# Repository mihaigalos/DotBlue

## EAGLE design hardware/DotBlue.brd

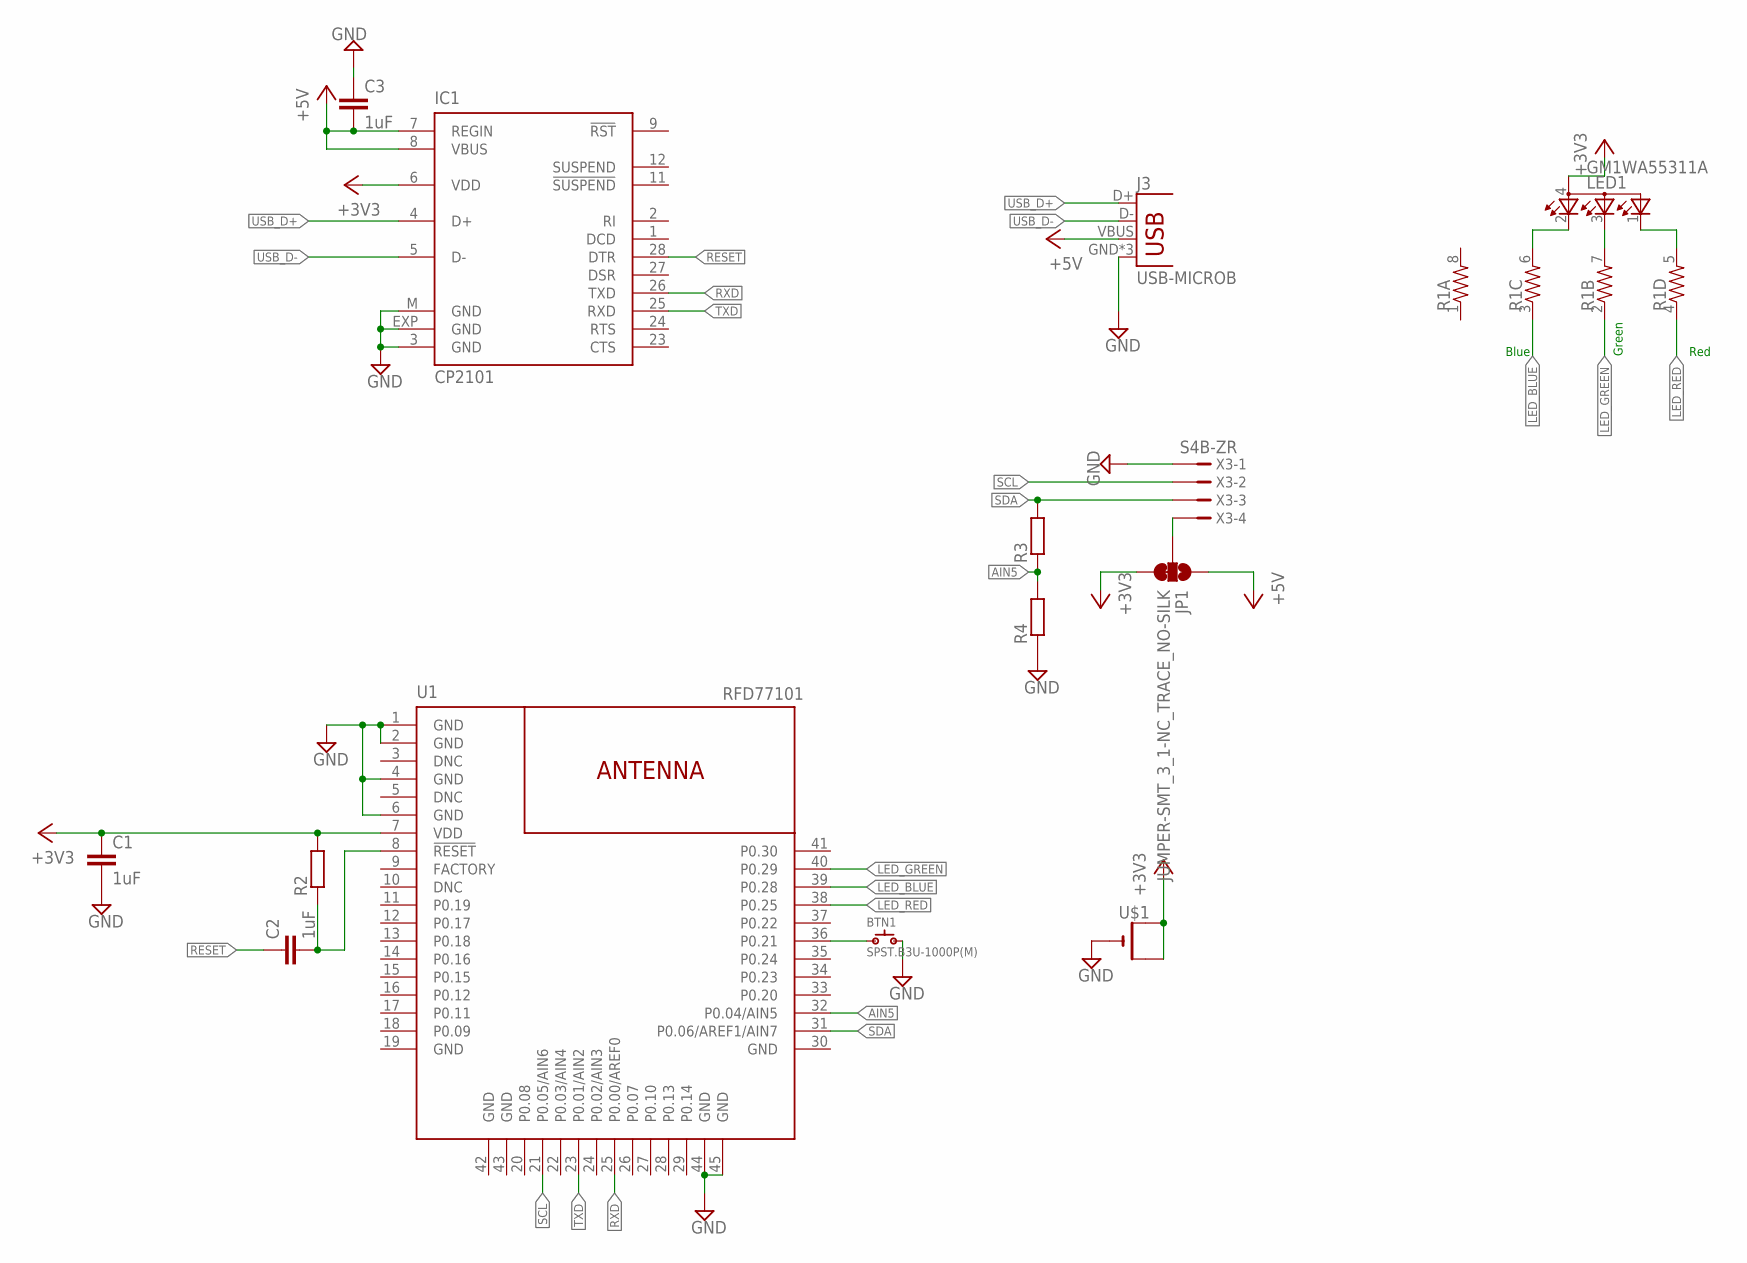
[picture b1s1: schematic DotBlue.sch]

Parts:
BTN1: SPST.B3U-1000P(M); B3U-1000P(M)
C1, C2, C3: 1uF; C0603
IC1: CP2101; MLP28
J3: USB-MICROB
JP1: JUMPER-SMT_3_1-NC_TRACE_NO-SILK; SMT-JUMPER_3_1-NC_TRACE_NO-SILK
LED1: GM1WA55311A
R1: RESISTOR-ARRAY0603-ARV; 0603-ARV
R2, R3, R4: R-EU_R0603; R0603
U1: RFD77101
U$1: CR1220SMT; CR1220-SMD
X3: S4B-ZR

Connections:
+3V3: C1.1, IC1.6 (VDD), JP1.3, LED1.4 (A), R2.2, U1.7 (VDD), U$1.+$1 (+), U$1.+$2 (+1)
+5V: C3.2, IC1.7 (REGIN), IC1.8 (VBUS), J3.VBUS, JP1.1
AIN5: R3.1, R4.2, U1.32 (P0.04/AIN5)
GND: BTN1.2, C1.2, C3.1, IC1.3 (GND), IC1.EXP (GND), IC1.M (GND), J3.GND, J3.MT1 (GND), J3.MT2 (GND), R4.1, U1.1 (GND), U1.2 (GND), U1.4 (GND), U1.6 (GND), U1.19 (GND), U1.30 (GND), U1.42 (GND), U1.43 (GND), U1.44 (GND), U1.45 (GND), U$1.-, X3.1
LED_BLUE: R1.3 (1), U1.39 (P0.28)
LED_GREEN: R1.2 (1), U1.40 (P0.29)
LED_RED: R1.4 (1), U1.38 (P0.25)
unnamed: LED1.3 (CBLUE), R1.7 (2)
unnamed: C2.2, R2.1, U1.8 (!RESET!)
unnamed: BTN1.1, U1.36 (P0.21)
unnamed: LED1.2 (CRED), R1.6 (2)
unnamed: JP1.2, X3.4
unnamed: LED1.1 (CGREEN), R1.5 (2)
RESET: C2.1, IC1.28 (DTR)
RXD: IC1.26 (TXD), U1.25 (P0.00/AREF0)
SCL: U1.21 (P0.05/AIN6), X3.2
SDA: R3.2, U1.31 (P0.06/AREF1/AIN7), X3.3
TXD: IC1.25 (RXD), U1.23 (P0.01/AIN2)
USB_D+: IC1.4 (D+), J3.D+
USB_D-: IC1.5 (D-), J3.D-

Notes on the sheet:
Blue
Green
Red

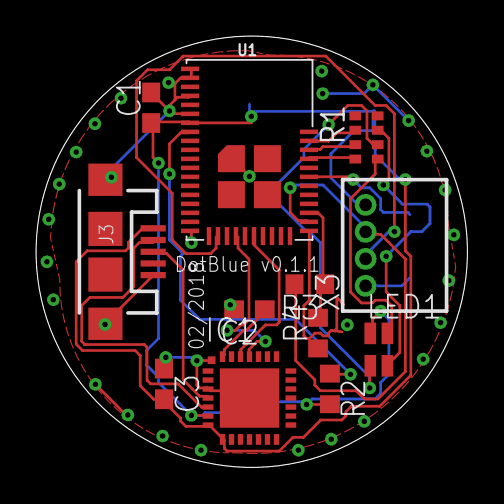
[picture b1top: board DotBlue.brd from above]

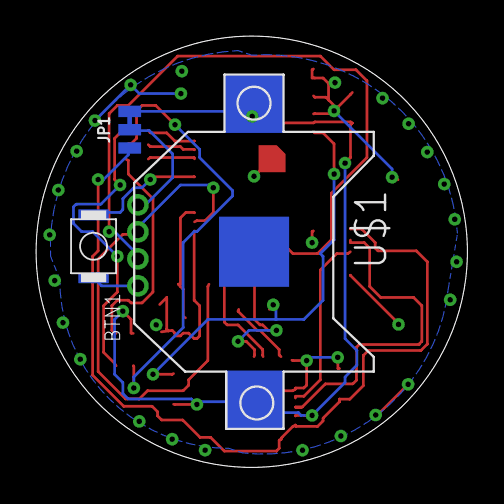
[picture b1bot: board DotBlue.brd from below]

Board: 2 copper layers, 24.0 x 24.0 mm, 15 parts (3 on the bottom side), 20 nets.

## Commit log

2017-12-15 Flip JST, add AIN
2017-12-15 Swap IO_AB for I2C pins, correct traces near pins, solidify GND
2017-12-15 Allign passive components
2017-12-15 Add 3-way JMP for 3V-5V switch of JST
2017-12-15 Add RGB connections
2017-12-15 Add UART connections
2017-12-15 Resolidify GND

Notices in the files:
parts and their libraries:
SparkFun-RF: Licensing: Creative Commons ShareAlike 4.0 International - https://creativecommons.org/licenses/by-sa/4.0
SparkFun-RF: © 2015 RF Digital Corporation
SparkFun: Licensing: CC v3.0 Share-Alike You are welcome to use this library for commercial purposes.
